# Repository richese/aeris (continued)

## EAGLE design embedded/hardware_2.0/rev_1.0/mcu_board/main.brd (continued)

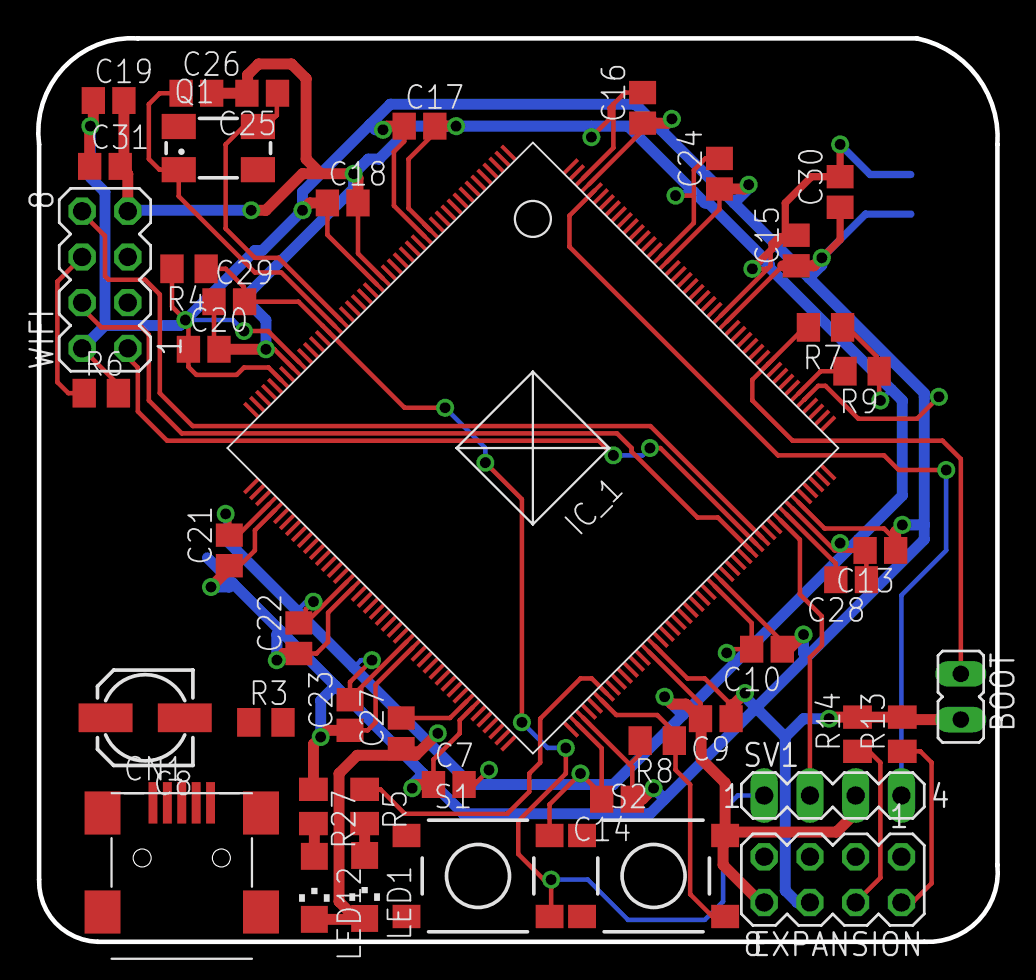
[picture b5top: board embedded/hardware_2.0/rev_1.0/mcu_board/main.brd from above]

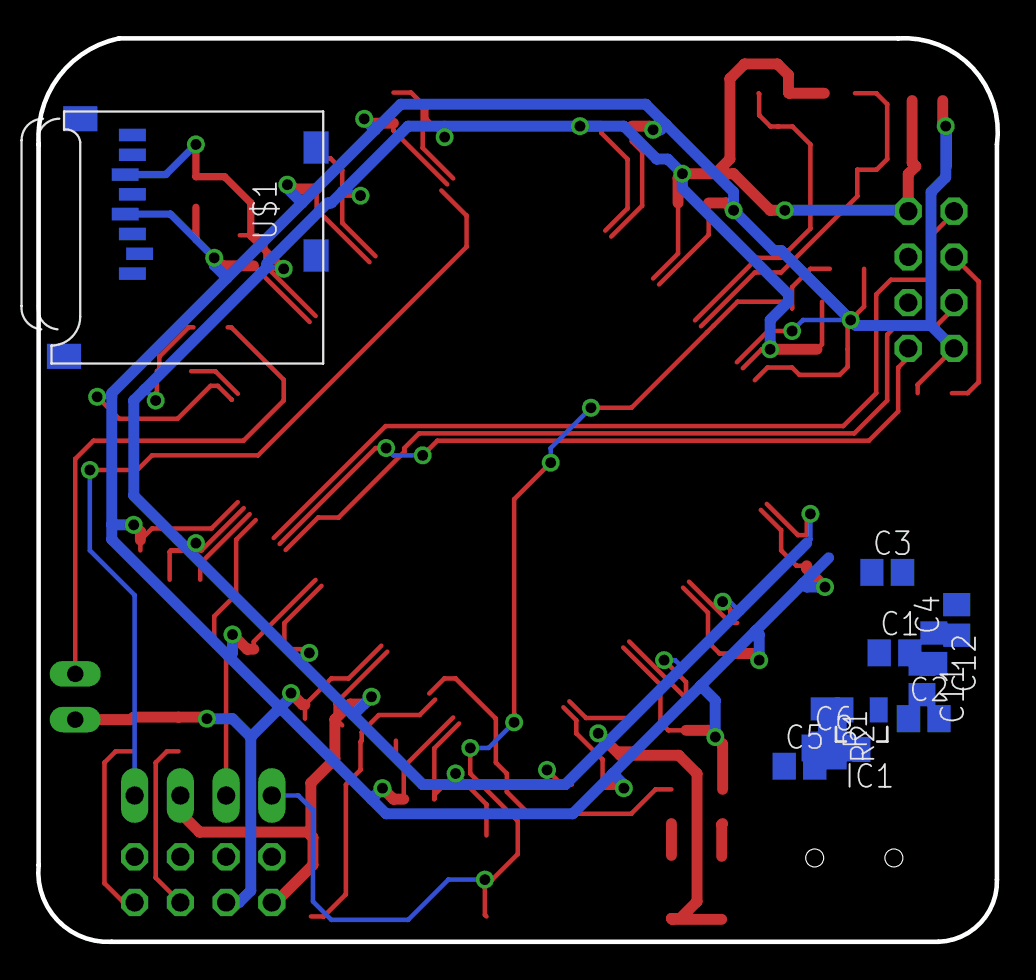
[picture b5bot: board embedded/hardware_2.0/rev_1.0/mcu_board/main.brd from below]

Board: 2 copper layers, 53.3 x 50.2 mm, 56 parts (12 on the bottom side), 27 nets.

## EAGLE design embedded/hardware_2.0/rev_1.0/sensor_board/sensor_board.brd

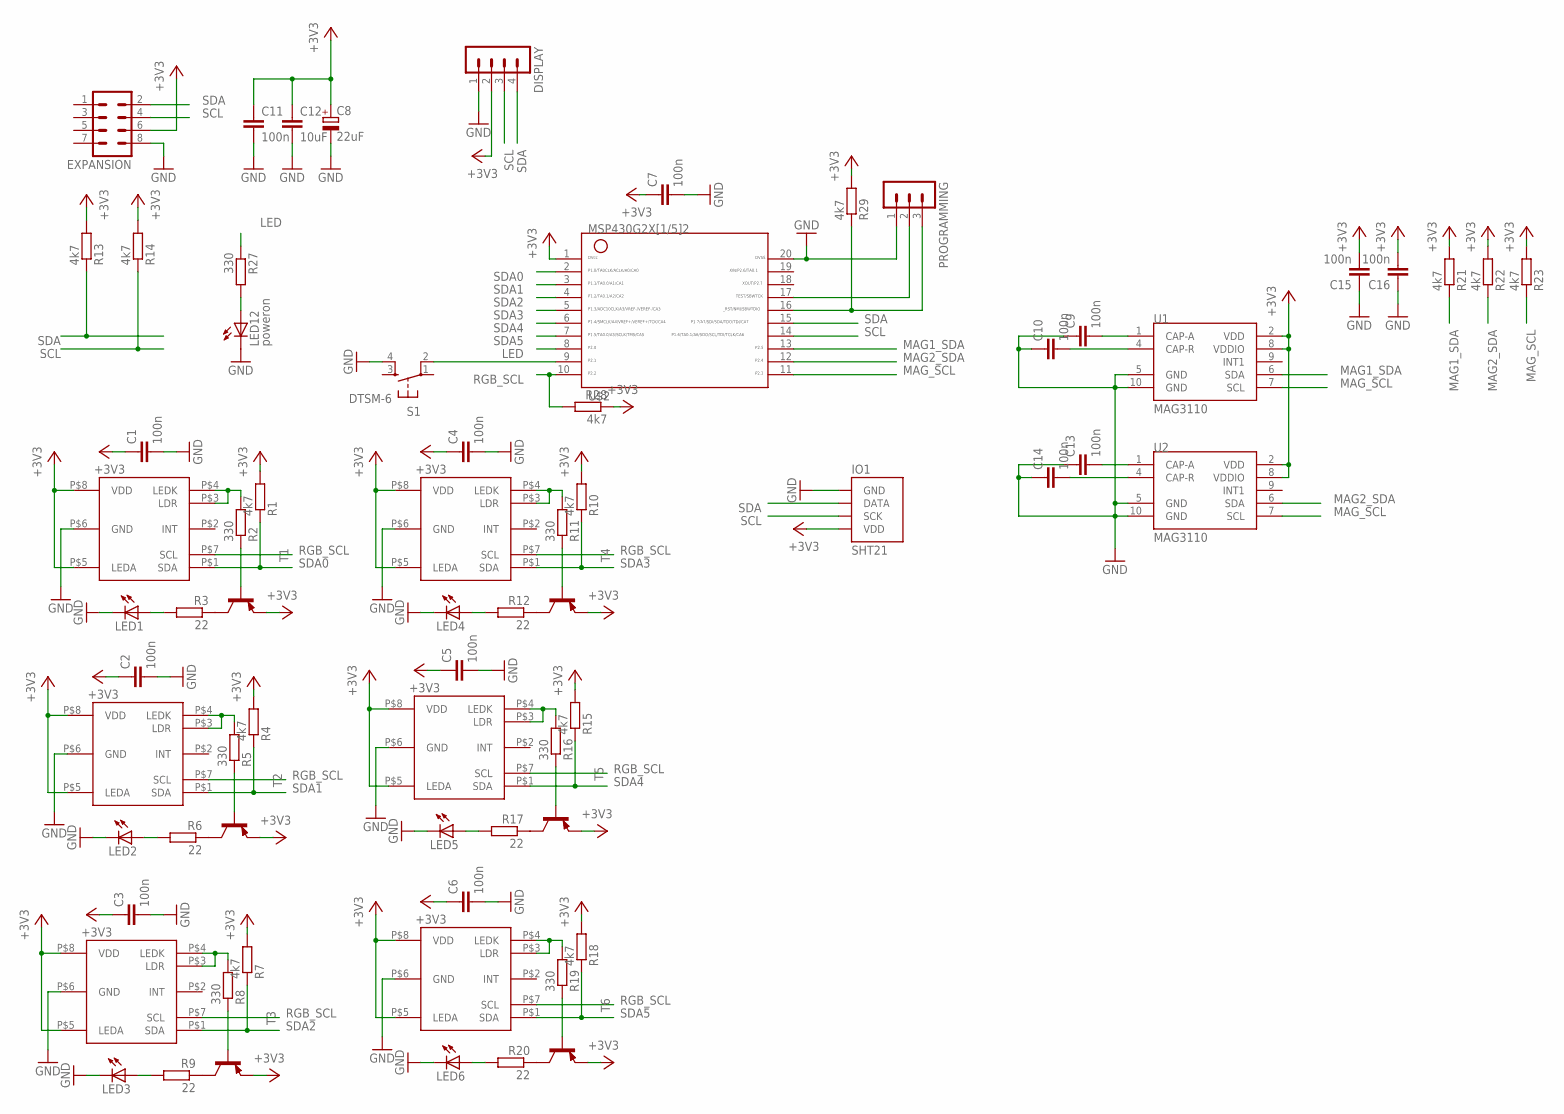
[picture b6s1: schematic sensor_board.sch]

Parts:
C1, C2, C3, C4, C5, C6, C7, C9, C10, C11, C13, C14, C15, C16: 100n; C0805
C8: 22uF; 153CLV-0505
C12: 10uF; C0805
DISPLAY: MA04-1
EXPANSION: MA04-2
IO1: SHT21; SHT2X
LED1, LED2, LED3, LED4, LED5, LED6: LED5MM
LED12: poweron; CHIPLED_1206
PROGRAMMING: MA03-1
R1, R4, R7, R10, R13, R14, R15, R18, R21, R22, R23, R28, R29: 4k7; M0805
R2, R5, R8, R11, R16, R19, R27: 330; M0805
R3, R6, R9, R12, R17, R20: 22; M0805
S1: DTSM-6
T1, T2, T3, T4, T5, T6: BC857A-PNP-SOT23-BEC; SOT23-BEC
U1, U2: MAG3110; DFN-10
U$1, U$3, U$4, U$5, U$6, U$7: APDS9950_EDGE
U$2: G2X[1/5]2---PW20; PW20

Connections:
+3V3: C1.1, C2.1, C3.1, C4.1, C5.1, C6.1, C7.1, C8.+, C11.1, C12.1, C15.2, C16.2, DISPLAY.2, EXPANSION.6, IO1.5 (VDD), R1.2, R4.2, R7.2, R10.2, R13.2, R14.2, R15.2, R18.2, R21.2, R22.2, R23.2, R28.1, R29.2, T1.E, T2.E, T3.E, T4.E, T5.E, T6.E, U1.2 (VDD), U1.8 (VDDIO), U2.2 (VDD), U2.8 (VDDIO), U$1.P$5 (LEDA), U$1.P$8 (VDD), U$2.1, U$3.P$5 (LEDA), U$3.P$8 (VDD), U$4.P$5 (LEDA), U$4.P$8 (VDD), U$5.P$5 (LEDA), U$5.P$8 (VDD), U$6.P$5 (LEDA), U$6.P$8 (VDD), U$7.P$5 (LEDA), U$7.P$8 (VDD)
GND: C1.2, C2.2, C3.2, C4.2, C5.2, C6.2, C7.2, C8.-, C9.1, C10.1, C11.2, C12.2, C13.1, C14.1, C15.1, C16.1, DISPLAY.1, EXPANSION.8, IO1.2 (GND), LED1.K (C), LED2.K (C), LED3.K (C), LED4.K (C), LED5.K (C), LED6.K (C), LED12.C, PROGRAMMING.1, S1.4, U1.5 (GND), U1.10 (GND), U2.5 (GND), U2.10 (GND), U$1.P$6 (GND), U$2.20, U$3.P$6 (GND), U$4.P$6 (GND), U$5.P$6 (GND), U$6.P$6 (GND), U$7.P$6 (GND)
LED: R27.1, U$2.8
MAG1_SDA: R21.1, U1.6 (SDA), U$2.13
MAG2_SDA: R22.1, U2.6 (SDA), U$2.12
MAG_SCL: R23.1, U1.7 (SCL), U2.7 (SCL), U$2.11
unnamed: R2.2, U$1.P$3 (LDR), U$1.P$4 (LEDK)
unnamed: PROGRAMMING.3, R29.1, U$2.16
unnamed: PROGRAMMING.2, U$2.17
unnamed: C10.2, U1.4 (CAP-R)
unnamed: C9.2, U1.1 (CAP-A)
unnamed: R2.1, T1.B
unnamed: R3.1, T1.C
unnamed: LED1.A, R3.2
unnamed: R5.2, U$3.P$3 (LDR), U$3.P$4 (LEDK)
unnamed: R5.1, T2.B
unnamed: R6.1, T2.C
unnamed: LED2.A, R6.2
unnamed: R8.2, U$4.P$3 (LDR), U$4.P$4 (LEDK)
unnamed: R8.1, T3.B
unnamed: R9.1, T3.C
unnamed: LED3.A, R9.2
unnamed: R11.2, U$5.P$3 (LDR), U$5.P$4 (LEDK)
unnamed: R11.1, T4.B
unnamed: R12.1, T4.C
unnamed: LED12.A, R27.2
unnamed: LED4.A, R12.2
unnamed: R16.2, U$6.P$3 (LDR), U$6.P$4 (LEDK)
unnamed: R16.1, T5.B
unnamed: R17.1, T5.C
unnamed: LED5.A, R17.2
unnamed: R19.2, U$7.P$3 (LDR), U$7.P$4 (LEDK)
unnamed: R19.1, T6.B
unnamed: R20.1, T6.C
unnamed: LED6.A, R20.2
unnamed: S1.2, U$2.9
unnamed: C13.2, U2.1 (CAP-A)
unnamed: C14.2, U2.4 (CAP-R)
RGB_SCL: R28.2, U$1.P$7 (SCL), U$2.10, U$3.P$7 (SCL), U$4.P$7 (SCL), U$5.P$7 (SCL), U$6.P$7 (SCL), U$7.P$7 (SCL)
SCL: DISPLAY.3, EXPANSION.4, IO1.4 (SCK), R14.1, U$2.14
SDA: DISPLAY.4, EXPANSION.2, IO1.1 (DATA), R13.1, U$2.15
SDA0: R1.1, U$1.P$1 (SDA), U$2.2
SDA1: R4.1, U$2.3, U$3.P$1 (SDA)
SDA2: R7.1, U$2.4, U$4.P$1 (SDA)
SDA3: R10.1, U$2.5, U$5.P$1 (SDA)
SDA4: R15.1, U$2.6, U$6.P$1 (SDA)
SDA5: R18.1, U$2.7, U$7.P$1 (SDA)

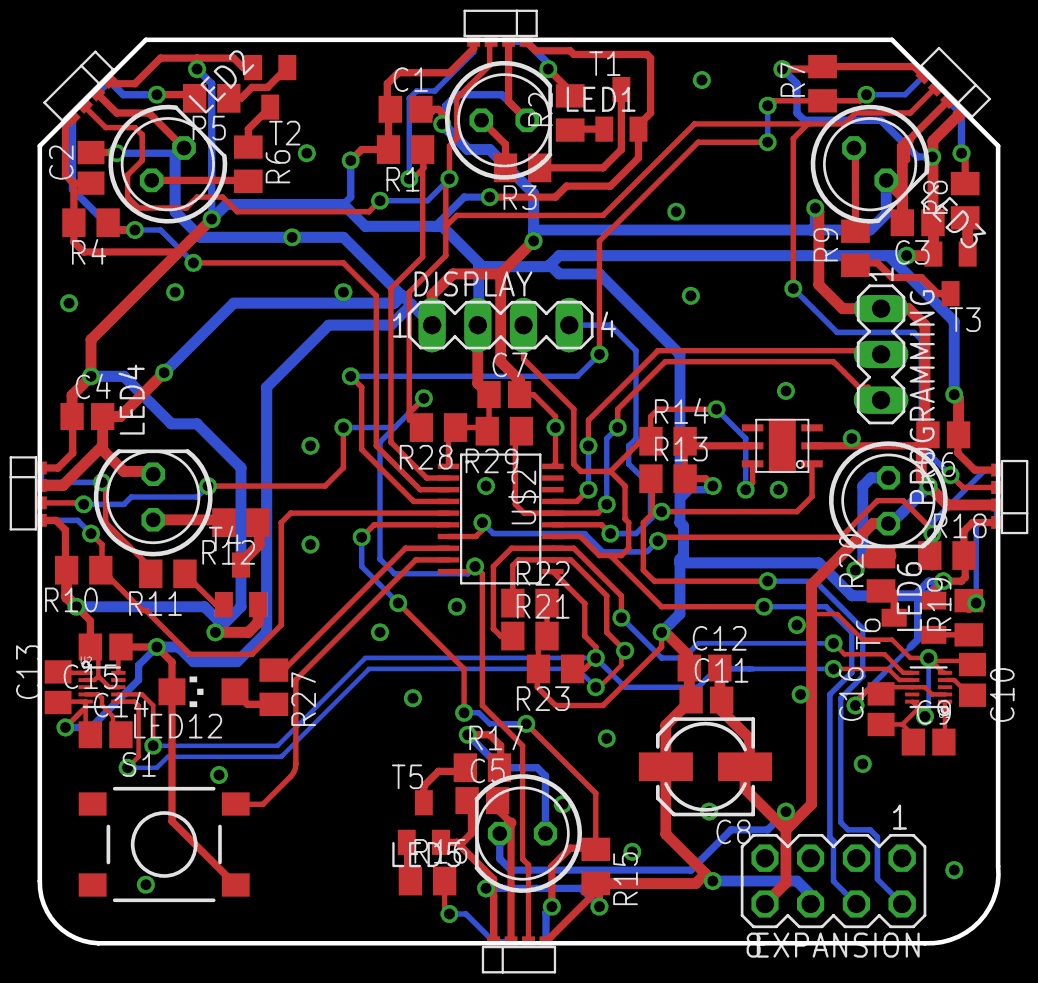
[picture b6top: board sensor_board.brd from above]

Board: 2 copper layers, 53.3 x 50.2 mm, 69 parts (0 on the bottom side), 47 nets.

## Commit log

2015-04-25 veriosn 1.0.2 added
2015-04-25 version 1.0.0 added
2015-04-25 common commit
2015-04-25 added robots suicide and gl_visualisation refresh group
2015-04-26 full pheromones support added and collective brain loading from files
2015-04-26 better pheromone spawning
2015-04-26 bin dirs added
2015-04-27 hardware release rev.1
2015-04-29 some work on Q learning
2015-04-30 work on wifi bootloader started
2015-05-01 work on wifi driver
2015-05-02 robot atomic packet container added, prepared for wifi communication
2015-05-02 clean up
2015-05-07 some work on ILC in ruby (in tmp)
2015-05-10 q-learning merging ability added, TODO: saving to file
2015-05-10 work on Qlearning saving
2015-05-10 brutal mess around Q learning cleaned up
2015-05-13 q leaning + agents works, TODO : Q matrix normalisation
2015-05-15 yeah, neural network on Q learning works!
2015-05-25 q learning tests
2015-06-01 some directories mess cleaned up
2015-06-15 kohonen + feed forward nn added as Q-table aproximation
2015-08-22 mess celaned up
2015-09-21 hal added
2015-09-23 line follower
2015-10-09 common
2016-02-08 new version
2016-02-11 cpu board
2016-02-19 aeris_2.0
2016-02-20 wifi driver added
2016-02-26 work on IMU
2016-02-26 rotation added
2016-02-28 sunday commit
2016-03-02 pictures + diagrams
2016-03-12 first version done
2016-03-13 we template
2016-03-15 visualsiation + line follower example
2016-03-15 picture
2016-03-29 Unified indent style of source files to tabs.
2016-04-06 color recognition
2016-04-06 micro bot added
2016-04-12 presentation
2016-05-03 Removed agent log files from git and added 'debug_log.txt', 'error_log.txt' to .gitignore. Rename 'run~' scripts to 'run'.
2016-05-03 Fix memory leak.
2016-05-03 Make it easier to pass optimization compiler flags.
2016-05-04 Bug fixes: - Join threads before calling delete on them. - Replace blocking call to `accept` in server loop with `select` with 1s timeout. Caused server to hang on shutdown. - Fix double free of `age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
2016-05-09 color_calib_bot base
